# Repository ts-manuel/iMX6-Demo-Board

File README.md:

# i.MX6 Demo Board

<!-- TABLE OF CONTENTS -->
<details open="open">
  <summary>Table of Contents</summary>
  <ol>
    <li><a href="#about-the-project">About The Project</a></li>
    <li><a href="#hardware-specifications">Hardware Specifications</a></li>
    <li><a href="#software">Software</a></li>
    <li><a href="#schematic">Schematic</a></li>
  </ol>
</details>

<!-- ABOUT THE PROJECT -->
## About The Project
This repository contains the design files and documentation for a custom-built Linux demo board based on the NXP i.MX6ULL (900 MHz ARM Cortex-A7). The purpose of this project isn't to solve a specific problem or build a commercial product. This is a dedicated learning platform designed to bridge the gap between simple micro-controllers and complex application processors. While micro-controllers (like STM32 or ESP32) are great for real-time tasks, application processors are better suited for "heavy lifting" and high-level software stacks. Checkout the full schematic [schematic](./kicad/schematic/iMX6%20Demo%20Board.pdf) and the <a href="https://htmlpreview.github.io/?https://github.com/ts-manuel/iMX6-Demo-Board/blob/main/kicad/bom/ibom.html" target="_blank">Interactive BOM</a>.

### Hardware Specifications
- **System**
    - CPU: NXP i.MX6ULL @ 900 MHz (ARM Cortex-A7)
    - RAM: 512 MB DDR3
- **Storage:**
    - 4 GB eMMC (On-board)
    - 32 MB NOR Quad SPI
    - Micro SD-Card Slot
- **Connectivity:**
    - 1x 100Mb Ethernet
    - 2x USB 2.0 Host (Type A)
    - 1x USB 2.0 Device (Type C)
    - 2x Audio Jacks 3.5 mm (WM8904 Codec)
- **UI & Indicators:**
    - 24-bit LCD Interface
    - 8x User LEDs + 5x Status LEDs

<!-- SOFTWARE -->
## Software
The current goal is to compile a basic Linux image using the Yocto Project to exercise and validate every hardware feature on the board (Ethernet, USB, Display, and GPIO).

**Status: In Progress**. Development of the custom meta-layer and bitbake recipes is currently underway.

<!-- SCHEMATIC -->
## Schematic
Checkout the full [schematic](./kicad/schematic/iMX6%20Demo%20Board.pdf) in PDF.

### POWER TREE

### BLOCK DIAGRAM

### POWER

### CPU

### RAM DDR3

### eMMC QSPI SD

### USB TYPE A

### ETHERNET

### AUDIO CODEC

### LCD

### BOOT CONFIG

### CONTROL GPIO

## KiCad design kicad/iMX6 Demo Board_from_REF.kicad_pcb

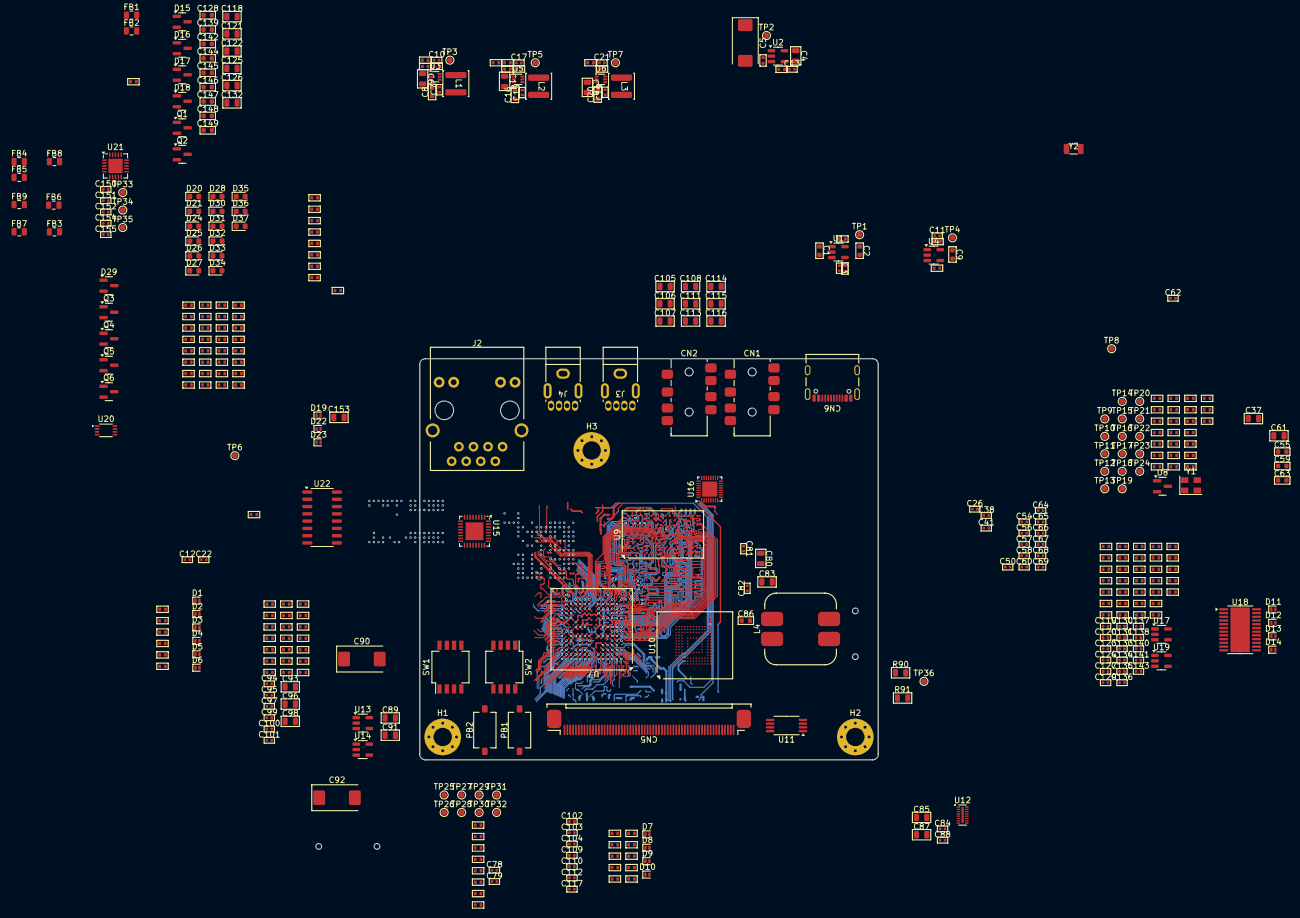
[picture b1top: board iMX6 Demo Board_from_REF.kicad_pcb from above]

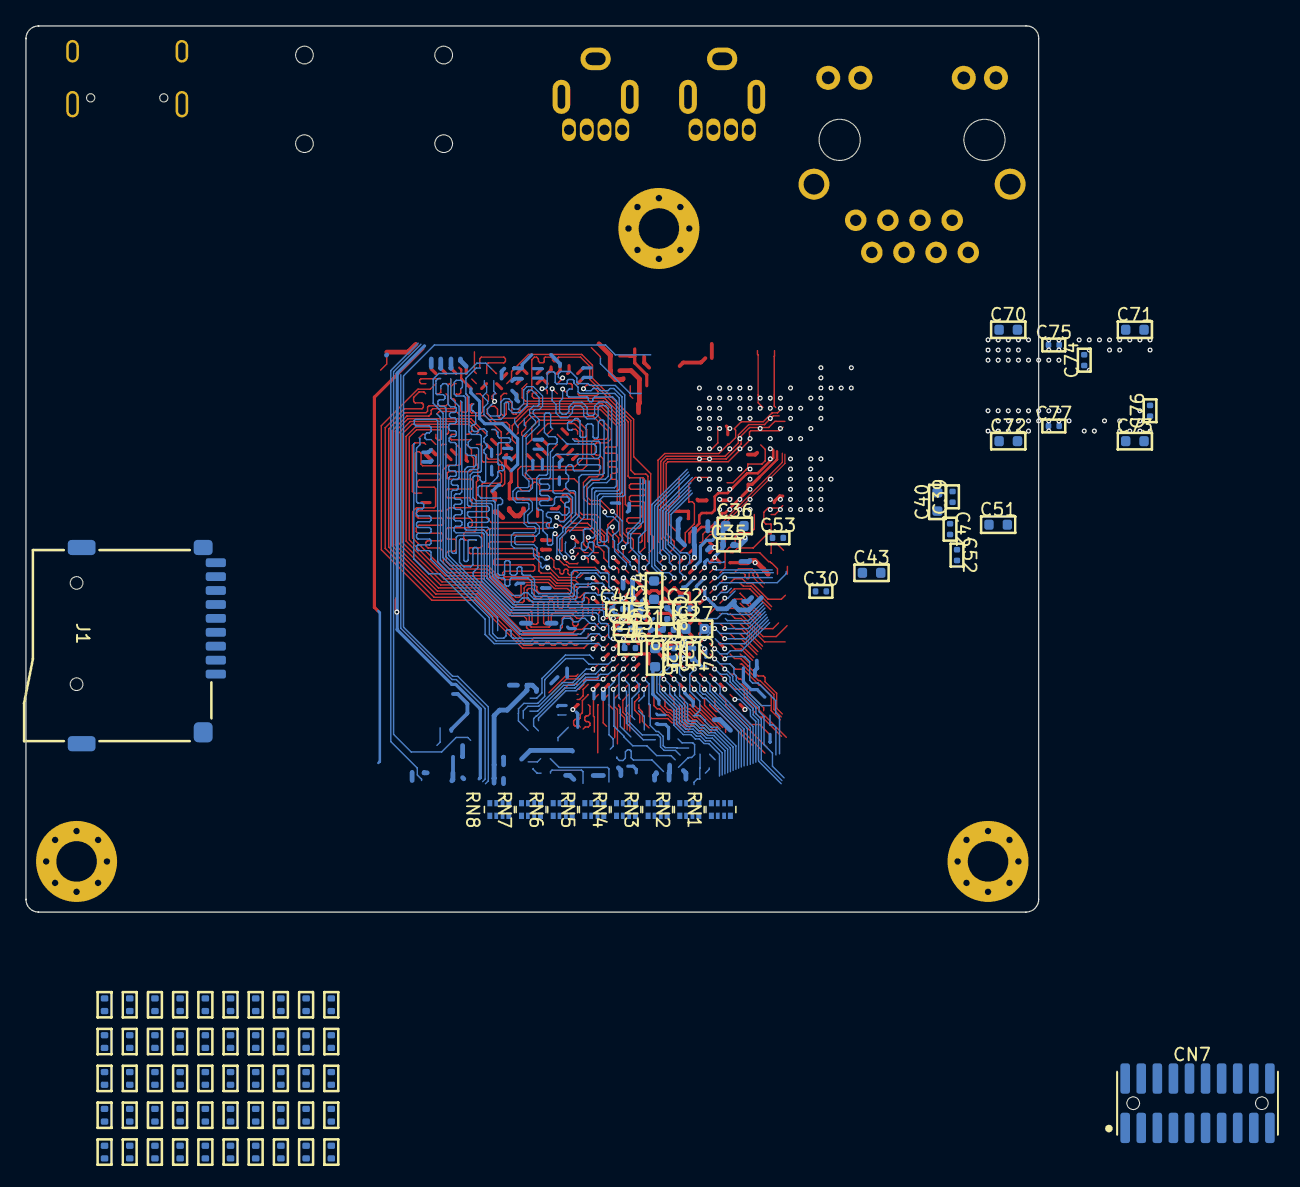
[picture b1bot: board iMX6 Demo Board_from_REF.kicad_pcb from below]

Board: 6 copper layers, 80.0 x 70.0 mm, 504 parts (91 on the bottom side), 405 nets.

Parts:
C1, C2, C8, C9, C16, C20, C55, C59, C63, C86, C128, C139, C142, C144, C145, C146, C147, C148, C149: 1 uF; CAP-0603
C3: 220 pF; CAP-0402
C4, C6, C14, C18, C80, C83, C85, C87, C89, C91, C98, C105, C106, C107, C108, C111, C113, C114, C115, C116, C118, C121, C122, C125, C126, C132, C153: 2.2 uF; CAP-0805
C5, C90, C92: 150 uF; CP_EIA-7343-31_Kemet-D
C7, C12, C13, C15, C19, C26, C50, C56, C57, C58, C60, C62, C64, C69, C78, C79, C81, C82, C84, C88, C94, C95, C97, C99, C100, C101, C102, C103, C104, C109, C110, C112, C117, C119, C120, C127, C130, C131, C133, C135, C140, C141, C143, C150, C151, C152, C154, C155: 100 nF; CAP-0402
C10, C17, C21, C65, C66, C67, C68, C123, C124, C129, C136: 22 pF; CAP-0402
C11: 560 pF; CAP-0402
C22, C134, C137, C138: 2.2 nF; CAP-0402
C23, C24, C28, C29, C30, C31, C32, C33, C35, C38, C39, C41, C42, C44, C45, C46, C52, C53, C54, C74, C75, C76, C77: 220 nF; CAP-0402
C25, C27, C34: 22 uF; CAP-0603
C36, C40, C43: 10 uF; CAP-0603
C37, C61, C93, C96: 22 uF; CAP-0805
C51, C70, C71, C72, C73: 2.2 uF; CAP-0603
CN1, CN2: PJ-393 8PJ; Jack_SMD_3.5mm_PJ-393-8PJ
CN5: KH-CL0.5-H2.0-60PS; CN-FPC-KH-CL0.5-H2.0-60PS
CN6: USB4105-GF-A; USB-TYPE-C-12P
CN7: 20021121-00020C4LF; CN-SMD-2x10P-1.27MM-FR
D1, D2, D3, D4, D5, D6, D7, D8, D9, D10, D11, D12, D13, D14, D19, D22, D23: LESD8D5.0CAT5G; D_SOD-882
D15, D16, D17, D18, D29: BAT54S; SOT-23
D20, D24: 150060RS75003; LED_0603_1608Metric
D21, D25, D26, D27, D28, D30, D31, D32, D33, D34, D35, D36, D37: 150060VS75000; LED_0603_1608Metric
FB1, FB2, FB3, FB4, FB5, FB6, FB7, FB8, FB9: GZ2012D101TF; FB-0805
H1, H2, H3: MountingHole_Pad; MountingHole_3.2mm_M3_Pad_Via
J1: GT-TF003-H0185-01; MicroSD_G-Switch _GT-TF003-H0185-01
J2: HR911105A; RJ45_THT-HR911105A
J3, J4: 906-762B1026D10200; USB-TypeA-906-762B1026D10200
L1, L2, L3: 27 uH; IND-SMD-FNR4020S
L4: 6.8 uH; IND-SMD-ACPR1208S
PB1, PB2: PTS636 SK25 SMTR LFS; BTN_SMD_PTS636-SK25-SMTR-LFS
Q1: NTR5105PT1G; SOT-23
Q2, Q3, Q4, Q5, Q6: SMMBT3904LT1G; SOT-23
R1: 56.2K; RES-0402
R2, R6, R8, R9, R10: 18K; RES-0402
R3, R5, R11, R12, R15, R116: 82K; RES-0402
R4: 24K; RES-0402
R7, R18, R19, R20, R23, R24, R29, R43, R44, R45, R49, R50, R51, R52, R53, R54, R55, R56, R57, R58, R61, R66, R67, R68, R72, R73, R74, R78, R79, R84, R86, R89, R92, R93, R94, R97, R98, R131, R132, R133, R134, R135, R136, R137, R138, R139, R140, R141, R142, R143, R144, R145, R146, R147, R148, R149, R150, R155, R156, R157, R158, R159, R160, R161, R162, R163, R164, R165, R166, R167, R168, R169, R170, R171, R172, R173, R174, R175, R176, R177, R178, R179, R180, R197, R198, R199, R200, R201, R202, R211, R212: 10K; RES-0402
R13: 72K; RES-0402
R14: 820R; RES-0402
R16: 64.9K; RES-0402
R17, R41, R42: 240R; RES-0402
R21, R25, R26, R104, R105, R107, R108, R109, R117, R119, R120, R123, R126: 0R; RES-0402
R22, R46, R47, R59, R60, R62, R69, R70, R71, R75, R76, R77, R80, R81, R82, R83, R85, R111, R112, R151, R152, R153, R154, R187, R188: 1.5K; RES-0402
R27, R28, R30, R31, R32, R33, R34, R35, R36, R37, R40: 1M; RES-0402
R38, R87, R88, R95, R96, R181, R182, R183, R184, R185, R186: 22R; RES-0402
R39, R63, R64, R99, R100, R101, R106, R191, R192, R193, R194, R195, R196, R203, R204, R205, R206, R207, R208, R209, R210: 220R; RES-0402
R48: 470R; RES-0402
R65: 6.49K; RES-0402
R90, R91: 100K; RES-0805
R102, R115: 62K; RES-0402
R103, R113, R114, R118: 680K; RES-0402
R110, R121, R122, R124, R125, R127, R128, R129, R130: 47K; RES-0402
R189, R190: 5.1K; RES-0402
RN1, RN2, RN3, RN4, RN5, RN6, RN7, RN8: 4x22R; R_Array_Convex_4x0402
SW1, SW2: EP-04KS; SW_DIP_SPSTx04_Slide_Copal_CHS-04B_W7.62mm_P1.27mm
TP1, TP2, TP3, TP4, TP5, TP6, TP7, TP8, TP9, TP10, TP11, TP12, TP13, TP14, TP15, TP16, TP17, TP18, TP19, TP20, TP21, TP22, TP23, TP24, TP25, TP26, TP27, TP28, TP29, TP30, TP31, TP32, TP33, TP34, TP35, TP36: TestPoint_Pad_D1.0mm
U1, U4: AP2127K-ADJTRG1; SOT-23-5
U2, U13, U14, U17: MT9700; SOT-23-5
U3, U5, U6: SY8892ARC; SOT-563
U7: MCIMX6Y2CVM08AB; BGA-289P08L17x17_14.0x14.0mm_Ball0.35mm_Pad0.30mm
U8: UM803RS; SOT-23
U9: MT41K256M16TW-107; BGA-96P08L9X16_8.0X14.0mm_Ball0.45_Pad0.40mm
U10: THGBMNG5D1LBAIL; BGA-153_13.0x11.5mm_Ball0.30mm_Pad0.25mm
U11: ZD25WQ80BOIGT; TSSOP-8_4.4x3mm_P0.65mm
U12: IP4252CZ16-8-TTL; Nexperia_HUSON-16_USON-16-1EP_1.35x3.3mm_P0.4mm_EP0.4x2.8mm
U15: KSZ8081RNBIA-TR; QFN-32-1EP_5x5mm_P0.5mm_EP3.1x3.1mm
U16: WM8904CGEFL/RV; QFN-32-1EP_4x4mm_P0.4mm_EP2.65x2.65mm
U18: TPS65150PWPR; HTSSOP-24-1EP_4.4x7.8mm_P0.65mm_EP3.4x7.8mm_Mask2.4x4.68mm
U19: LMV321IDBVR; SOT-23-5
U20: TXS0102DCUR; VSSOP-8_2.3x2mm_P0.5mm
U21: FT231XQ; QFN-20-1EP_4x4mm_P0.5mm_EP2.5x2.5mm
U22: 74HC595D,118; SO-16_3.9x9.9mm_P1.27mm
Y1: 24 MHz; Crystal_SMD_EuroQuartz_MT-4Pin_3.2x2.5mm
Y2: 32.768 KHz; QUARTZ-SC-32S32.768kHz20PPM12.5pF

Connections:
+1.8V: C9.1, C11.2, C26.1, C56.1, C80.1, C81.1, C84.1, C85.1, C102.2, C103.2, C107.1, C108.1, C109.2, FB7.1, R4.2, R49.1, R92.1, R93.1, TP4.1, U4.5 (VOUT), U7.E7 (NVCC_NAND), U7.F4 (NVCC_CSI), U10.C6 (VCCQ), U10.M4 (VCCQ), U10.N4 (VCCQ), U10.P3 (VCCQ), U10.P5 (VCCQ), U11.8 (VCC), U16.4 (DBVDD), U16.6 (DCVDD), U16.7 (CPVDD), U16.19 (MICVDD)
+3V3_DCDC: C7.1, C8.1, C10.2, C50.1, C62.1, C63.1, C64.1, C69.1, C82.1, C83.1, C93.1, C94.2, C152.1, CN7.2, FB1.1, FB2.1, FB3.1, FB6.2, J2.9 (GA), J2.12 (YA), L1.2, R5.2, R23.1, R24.1, R50.2, R51.2, R52.2, R53.2, R54.2, R55.2, R56.2, R59.1, R60.1, R61.1, R62.1, R66.2, R67.2, R68.2, R72.2, R73.2, R74.2, R78.2, R79.2, R84.2, R119.1, R131.1, R132.1, R133.1, R134.1, R135.1, R136.1, R137.1, R138.1, R139.1, R140.1, R141.1, R142.1, R143.1, R144.1, R145.1, R146.1, R147.1, R148.1, R149.1, R150.1, R151.1, R152.1, R153.1, R154.1, R155.1, R156.1, R191.1, R192.1, R193.1, R194.1, R195.1, R196.1, R203.1, R204.1, R205.1, R206.1, R207.1, R208.1, R209.1, R210.1, R211.1, TP3.1, U4.1 (VDD), U7.C4 (NVCC_SD1), U7.E13 (NVCC_LCD), U7.F13 (NVCC_ENET), U7.H13 (NVCC_UART), U7.J13 (NVCC_GPIO), U8.3 (VCC), U10.E6 (VCC), U10.F5 (VCC), U10.J10 (VCC), U10.K9 (VCC), U15.17 (VDDIO), U20.3 (VCCA), U22.16 (VCC)
+3V3_FTDI: C150.1, C151.1, C155.2, R187.2, R188.2, U20.7 (VCCB), U21.10 (3V3OUT), U21.11 (~REST), U21.20 (VCCIO)
+3V3_STAND_BY: C2.1, C3.2, C41.1, R1.2, TP1.1, U1.5 (VOUT), U7.P12 (VDD_SNVS_IN)
+5V_LCD: C119.1, C140.1, FB8.1, R124.2, R125.2, U17.1 (VOUT)
+5V_VBUS: C1.1, C4.1, C89.1, C91.1, C118.1, CN6.2 (VBUS), CN6.11 (VBUS), D19.2 (A2), FB9.1, U1.1 (VDD), U1.3 (EN), U2.5 (VIN), U13.5 (VIN), U14.5 (VIN), U17.5 (VIN)
+5V_VBUS_USB1: C55.1, C90.1, FB4.1, U7.T12 (USB_OTG1_VBUS), U13.1 (VOUT)
+5V_VBUS_USB2: C59.1, C92.1, FB5.1, U7.U12 (USB_OTG2_VBUS), U14.1 (VOUT)
+VDD_DRAM: C19.1, C20.1, C21.2, C43.1, C44.1, C45.1, C46.1, C70.1, C71.1, C72.1, C73.1, C74.1, C75.1, C76.1, C77.1, C78.1, L3.2, R15.2, R46.1, TP7.1, U7.G6 (NVCC_DRAM), U7.H6 (NVCC_DRAM), U7.J6 (NVCC_DRAM), U7.K6 (NVCC_DRAM), U7.L6 (NVCC_DRAM), U7.M6 (NVCC_DRAM), U9.A1 (VDDQ), U9.A8 (VDDQ), U9.B2 (VDD), U9.C1 (VDDQ), U9.C9 (VDDQ), U9.D2 (VDDQ), U9.D9 (VDD), U9.E9 (VDDQ), U9.F1 (VDDQ), U9.G7 (VDD), U9.H2 (VDDQ), U9.H9 (VDDQ), U9.K2 (VDD), U9.K8 (VDD), U9.N1 (VDD), U9.N9 (VDD), U9.R1 (VDD), U9.R9 (VDD)
+VDD_HIGH_CAP: C35.1, C36.1, C53.1, TP10.1, U7.N6 (NVCC_DRAM_2P5), U7.R14 (VDD_HIGH_CAP), U7.R15 (VDD_HIGH_CAP)
+VDD_SOC: C15.1, C16.1, C17.2, C27.1, C28.1, C29.1, C30.1, L2.2, R12.2, TP5.1, U7.H9 (VDD_SOC_IN), U7.H10 (VDD_SOC_IN), U7.J9 (VDD_SOC_IN), U7.J10 (VDD_SOC_IN), U7.K9 (VDD_SOC_IN), U7.K10 (VDD_SOC_IN)
/i.MX6ULL MAIN/AUDIO CODEC/I2C1.SCL: R92.2, U7.E5 (CSI_PIXCLK), U16.2 (SCLK)
/i.MX6ULL MAIN/AUDIO CODEC/I2C1.SDA: R93.2, U7.F5 (CSI_MCLK), U16.3 (SDA)
/i.MX6ULL MAIN/AUDIO CODEC/I2S_ADCDAT: U7.D2 (CSI_DATA06), U16.31 (ADCDAT)
/i.MX6ULL MAIN/AUDIO CODEC/I2S_BCLK: U7.D3 (CSI_DATA05), U16.29 (BCLK_/_GPIO4)
/i.MX6ULL MAIN/AUDIO CODEC/I2S_DACDAT: U7.D1 (CSI_DATA07), U16.32 (DACDAT)
/i.MX6ULL MAIN/AUDIO CODEC/I2S_LRCLK: U7.D4 (CSI_DATA04), U16.30 (LRCLK)
/i.MX6ULL MAIN/AUDIO CODEC/I2S_MCLK: U7.E3 (CSI_DATA01), U16.28 (MCLK)
/i.MX6ULL MAIN/BOOT CONFIG/BOOT_MODE_0: SW2.2, U7.T10 (BOOT_MODE0)
/i.MX6ULL MAIN/BOOT CONFIG/BOOT_MODE_1: SW2.1, U7.U10 (BOOT_MODE1)
/i.MX6ULL MAIN/BOOT CONFIG/LCD_DATA0: R157.1, RN2.6 (R3.2), SW1.4, U7.B9 (LCD_DATA00)
/i.MX6ULL MAIN/BOOT CONFIG/LCD_DATA1: R150.2, R158.1, RN2.7 (R2.2), U7.A9 (LCD_DATA01)
/i.MX6ULL MAIN/BOOT CONFIG/LCD_DATA2: R149.2, R159.1, RN2.8 (R1.2), U7.E10 (LCD_DATA02)
/i.MX6ULL MAIN/BOOT CONFIG/LCD_DATA3: R148.2, R160.1, RN3.5 (R4.2), U7.D10 (LCD_DATA03)
/i.MX6ULL MAIN/BOOT CONFIG/LCD_DATA4: R147.2, R161.1, RN3.6 (R3.2), U7.C10 (LCD_DATA04)
/i.MX6ULL MAIN/BOOT CONFIG/LCD_DATA5: R162.1, RN3.7 (R2.2), SW1.3, U7.B10 (LCD_DATA05)
/i.MX6ULL MAIN/BOOT CONFIG/LCD_DATA6: R163.1, RN3.8 (R1.2), SW1.2, U7.A10 (LCD_DATA06)
/i.MX6ULL MAIN/BOOT CONFIG/LCD_DATA7: R164.1, RN4.5 (R4.2), SW1.1, U7.D11 (LCD_DATA07)
/i.MX6ULL MAIN/BOOT CONFIG/LCD_DATA8: R146.2, R165.1, RN4.6 (R3.2), U7.B11 (LCD_DATA08)
/i.MX6ULL MAIN/BOOT CONFIG/LCD_DATA9: R145.2, R166.1, RN4.7 (R2.2), U7.A11 (LCD_DATA09)
/i.MX6ULL MAIN/BOOT CONFIG/LCD_DATA10: R144.2, R167.1, RN4.8 (R1.2), U7.E12 (LCD_DATA10)
/i.MX6ULL MAIN/BOOT CONFIG/LCD_DATA11: R143.2, R168.1, RN5.5 (R4.2), U7.D12 (LCD_DATA11)
/i.MX6ULL MAIN/BOOT CONFIG/LCD_DATA12: R142.2, R169.1, RN5.6 (R3.2), U7.C12 (LCD_DATA12)
/i.MX6ULL MAIN/BOOT CONFIG/LCD_DATA13: R141.2, R170.1, RN5.7 (R2.2), U7.B12 (LCD_DATA13)
/i.MX6ULL MAIN/BOOT CONFIG/LCD_DATA14: R140.2, R171.1, RN5.8 (R1.2), U7.A12 (LCD_DATA14)
/i.MX6ULL MAIN/BOOT CONFIG/LCD_DATA15: R139.2, R172.1, RN6.5 (R4.2), U7.D13 (LCD_DATA15)
/i.MX6ULL MAIN/BOOT CONFIG/LCD_DATA16: R138.2, R173.1, RN6.6 (R3.2), U7.C13 (LCD_DATA16)
/i.MX6ULL MAIN/BOOT CONFIG/LCD_DATA17: R137.2, R174.1, RN6.7 (R2.2), U7.B13 (LCD_DATA17)
/i.MX6ULL MAIN/BOOT CONFIG/LCD_DATA18: R136.2, R175.1, RN6.8 (R1.2), U7.A13 (LCD_DATA18)
/i.MX6ULL MAIN/BOOT CONFIG/LCD_DATA19: R135.2, R176.1, RN7.5 (R4.2), U7.D14 (LCD_DATA19)
/i.MX6ULL MAIN/BOOT CONFIG/LCD_DATA20: R134.2, R177.1, RN7.6 (R3.2), U7.C14 (LCD_DATA20)
/i.MX6ULL MAIN/BOOT CONFIG/LCD_DATA21: R133.2, R178.1, RN7.7 (R2.2), U7.B14 (LCD_DATA21)
/i.MX6ULL MAIN/BOOT CONFIG/LCD_DATA22: R132.2, R179.1, RN7.8 (R1.2), U7.A14 (LCD_DATA22)
/i.MX6ULL MAIN/BOOT CONFIG/LCD_DATA23: R131.2, R180.1, RN8.5 (R4.2), U7.B16 (LCD_DATA23)
/i.MX6ULL MAIN/BOOT CONFIG/LCD_DOTCLK: CN5.44, RN8.1 (R1.1), RN8.8 (R1.2), U7.A8 (LCD_CLK)
/i.MX6ULL MAIN/BOOT CONFIG/LCD_HSYNC: CN5.42, RN8.3 (R3.1), RN8.6 (R3.2), U7.D9 (LCD_HSYNC)
/i.MX6ULL MAIN/BOOT CONFIG/LCD_RESET: CN5.14, RN1.3 (R3.1), RN1.6 (R3.2), U7.E9 (LCD_RESET)
/i.MX6ULL MAIN/BOOT CONFIG/LCD_VSYNC: CN5.43, RN8.2 (R2.1), RN8.7 (R2.2), U7.C9 (LCD_VSYNC)
/i.MX6ULL MAIN/CONTROL GPIO/FTDI_RX: D21.1 (K), R183.1, TP34.1, U21.1 (RXD)
/i.MX6ULL MAIN/CONTROL GPIO/FTDI_TX: D20.1 (K), R181.1, TP33.1, U21.17 (TXD)
/i.MX6ULL MAIN/CONTROL GPIO/JTAG_DACK: CN7.19, R201.1
/i.MX6ULL MAIN/CONTROL GPIO/JTAG_RTCK: CN7.11, R202.1
/i.MX6ULL MAIN/CONTROL GPIO/JTAG_TCK: CN7.9, U7.M14 (JTAG_TCK)
/i.MX6ULL MAIN/CONTROL GPIO/JTAG_TDI: CN7.5, U7.N16 (JTAG_TDI)
/i.MX6ULL MAIN/CONTROL GPIO/JTAG_TDO: CN7.13, U7.N15 (JTAG_TDO)
/i.MX6ULL MAIN/CONTROL GPIO/JTAG_TMS: CN7.7, U7.P14 (JTAG_TMS)
/i.MX6ULL MAIN/CONTROL GPIO/JTAG_VREF: CN7.1, R196.2
/i.MX6ULL MAIN/CONTROL GPIO/LED_ACTIVITY: R197.2, U7.G14 (~UART3_RTS)
/i.MX6ULL MAIN/CONTROL GPIO/LED_EMMC: R198.2, U7.H16 (UART3_RX_DATA)
/i.MX6ULL MAIN/CONTROL GPIO/LED_NETWORK: R200.2, U7.J15 (~UART2_CTS)
/i.MX6ULL MAIN/CONTROL GPIO/LED_SD: R199.2, U7.H17 (UART3_TX_DATA)
/i.MX6ULL MAIN/CONTROL GPIO/LED_SR_RCLK: U7.G17 (UART4_TX_DATA), U22.12 (RCLK)
/i.MX6ULL MAIN/CONTROL GPIO/LED_SR_SER: U7.G13 (UART5_RX_DATA), U22.14 (SER)
/i.MX6ULL MAIN/CONTROL GPIO/LED_SR_SRCLK: U7.F17 (UART5_TX_DATA), U22.11 (SRCLK)
/i.MX6ULL MAIN/CONTROL GPIO/PMIC_POWER_GOOD: R11.2, R21.2, TP6.1, U5.6 (PG), U6.6 (PG), U13.4 (EN), U14.4 (EN), U17.4 (EN), U20.6 (OE)
/i.MX6ULL MAIN/CONTROL GPIO/UART1.RX: R182.2, U7.K16 (UART1_RX_DATA)
/i.MX6ULL MAIN/CONTROL GPIO/UART1.TX: R184.2, U7.K14 (UART1_TX_DATA)
/i.MX6ULL MAIN/CONTROL GPIO/USBD_n: CN6.5 (DN2), CN6.7 (DN1), D22.2 (A2), R186.1
/i.MX6ULL MAIN/CONTROL GPIO/USBD_p: CN6.6 (DP1), CN6.8 (DP2), D23.2 (A2), R185.1
/i.MX6ULL MAIN/CONTROL GPIO/~JTAG_SRST: CN7.15, D29.3 (common)
/i.MX6ULL MAIN/CONTROL GPIO/~JTAG_TRST: CN7.3, U7.N14 (JTAG_TRST_B)
/i.MX6ULL MAIN/CONTROL GPIO/~LED_SR_SRCLR: U7.G16 (UART4_RX_DATA), U22.10 (~SRCLR)
/i.MX6ULL MAIN/CPU/DRAM_A0: TP28.1, U7.L5 (DRAM_ADDR00), U9.N3 (A0)
/i.MX6ULL MAIN/CPU/DRAM_A1: U7.H2 (DRAM_ADDR01), U9.P7 (A1)
/i.MX6ULL MAIN/CPU/DRAM_A2: U7.K1 (DRAM_ADDR02), U9.P3 (A2)
/i.MX6ULL MAIN/CPU/DRAM_A3: U7.M2 (DRAM_ADDR03), U9.N2 (A3)
/i.MX6ULL MAIN/CPU/DRAM_A4: U7.K4 (DRAM_ADDR04), U9.P8 (A4)
/i.MX6ULL MAIN/CPU/DRAM_A5: U7.L1 (DRAM_ADDR05), U9.P2 (A5)
/i.MX6ULL MAIN/CPU/DRAM_A6: U7.G2 (DRAM_ADDR06), U9.R8 (A6)
/i.MX6ULL MAIN/CPU/DRAM_A7: U7.H4 (DRAM_ADDR07), U9.R2 (A7)
/i.MX6ULL MAIN/CPU/DRAM_A8: U7.J4 (DRAM_ADDR08), U9.T8 (A8)
/i.MX6ULL MAIN/CPU/DRAM_A9: U7.L2 (DRAM_ADDR09), U9.R3 (A9)
/i.MX6ULL MAIN/CPU/DRAM_A10: U7.M4 (DRAM_ADDR10), U9.L7 (A10/AP)
/i.MX6ULL MAIN/CPU/DRAM_A11: U7.K3 (DRAM_ADDR11), U9.R7 (A11)
/i.MX6ULL MAIN/CPU/DRAM_A12: U7.L4 (DRAM_ADDR12), U9.N7 (A12/~BC)
/i.MX6ULL MAIN/CPU/DRAM_A13: U7.H3 (DRAM_ADDR13), U9.T3 (A13)
/i.MX6ULL MAIN/CPU/DRAM_A14: U7.G1 (DRAM_ADDR14), U9.T7 (A14)
/i.MX6ULL MAIN/CPU/DRAM_A15: U7.K5 (DRAM_ADDR15), U9.M7 (NC_(A15))
/i.MX6ULL MAIN/CPU/DRAM_BA0: U7.M1 (DRAM_SDBA0), U9.M2 (BA0)
/i.MX6ULL MAIN/CPU/DRAM_BA1: U7.H1 (DRAM_SDBA1), U9.N8 (BA1)
/i.MX6ULL MAIN/CPU/DRAM_BA2: U7.K2 (DRAM_SDBA2), U9.M3 (BA2)
/i.MX6ULL MAIN/CPU/DRAM_CLK_EN0: R19.1, R45.1, U7.M3 (DRAM_SDCKE0), U9.K9 (CKE0)
/i.MX6ULL MAIN/CPU/DRAM_CLK_EN1: R20.1, R44.1, U7.J3 (DRAM_SDCKE1), U9.J9 (NC_(CKE1))
/i.MX6ULL MAIN/CPU/DRAM_CLK_N: R48.2, TP32.1, U7.P2 (DRAM_SDCLK0_N), U9.K7 (~CK)
/i.MX6ULL MAIN/CPU/DRAM_CLK_P: R48.1, TP26.1, U7.P1 (DRAM_SDCLK0_P), U9.J7 (CK)
/i.MX6ULL MAIN/CPU/DRAM_ODT0: U7.N1 (DRAM_ODT0), U9.K1 (ODT0)
/i.MX6ULL MAIN/CPU/DRAM_ODT1: U7.F1 (DRAM_ODT1), U9.J1 (NC_(ODT1))
/i.MX6ULL MAIN/CPU/ENET_CLK: R38.2, U15.9 (XI)
/i.MX6ULL MAIN/CPU/LCD_BACK_LIGHT: R112.1, U7.H15 (~UART3_CTS)
/i.MX6ULL MAIN/CPU/LCD_SPI_MOSI: RN2.5 (R4.2), U7.B15 (ENET2_TX_EN)
/i.MX6ULL MAIN/CPU/LCD_SPI_SCLK: RN1.8 (R1.2), U7.A16 (ENET2_TX_DATA1)
/i.MX6ULL MAIN/CPU/NVCC_PLL: C39.1, C40.1, TP11.1, U7.P13 (NVCC_PLL)
/i.MX6ULL MAIN/CPU/ONOFF: C57.1, PB1.2, R23.2, U7.R8 (ONOFF)
/i.MX6ULL MAIN/CPU/PMIC_ON_REQ: R10.1, U7.T9 (SNVS_PMIC_ON_REQ)
/i.MX6ULL MAIN/CPU/QSPI_DATA0: U7.A3 (~NAND_READY), U11.5 (SI/DQ0)
/i.MX6ULL MAIN/CPU/QSPI_DATA1: U7.C5 (~NAND_CE0), U11.2 (SO/DQ1)
/i.MX6ULL MAIN/CPU/QSPI_DATA2: U7.B5 (~NAND_CE1), U11.3 (~WP/DQ2)
/i.MX6ULL MAIN/CPU/QSPI_DATA3: U7.A4 (NAND_CLE), U11.7 (~HOLD/DQ3)
/i.MX6ULL MAIN/CPU/QSPI_SCLK: U7.D5 (~NAND_WP), U11.6 (SCLK)
/i.MX6ULL MAIN/CPU/RMII_CRS_DV/CONFIG2: R74.1, R77.1, U7.E16 (ENET1_RX_EN), U15.18 (CRS_DV/CONFIG2)
/i.MX6ULL MAIN/CPU/RMII_MDC: R59.2, U7.C16 (ENET2_RX_DATA1), U15.12 (MDC)
/i.MX6ULL MAIN/CPU/RMII_MDIO: R60.2, U7.C17 (ENET2_RX_DATA0), U15.11 (MDIO)
/i.MX6ULL MAIN/CPU/RMII_RXD0/DUPLEX: R83.1, U7.F16 (ENET1_RX_DATA0), U15.16 (RXD0/DUPLEX)
/i.MX6ULL MAIN/CPU/RMII_RXD1/PHYAD2: R68.1, R71.1, U7.E17 (ENET1_RX_DATA1), U15.15 (RXD1/PHYAD2)
/i.MX6ULL MAIN/CPU/RMII_RXER/ISO: R78.1, R80.1, U7.D15 (ENET1_RX_ER), U15.20 (RXER/ISO)
/i.MX6ULL MAIN/CPU/RMII_TXD0: U7.E15 (ENET1_TX_DATA0), U15.24 (TXD0)
/i.MX6ULL MAIN/CPU/RMII_TXD1: U7.E14 (ENET1_TX_DATA1), U15.25 (TXD1)
/i.MX6ULL MAIN/CPU/RMII_TXEN: U7.F15 (ENET1_TX_EN), U15.23 (TXEN)
/i.MX6ULL MAIN/CPU/SD_CARD_CMD: R54.1, U7.C2 (SD1_CMD), U12.3 (CH3)
/i.MX6ULL MAIN/CPU/SD_CARD_DATA0: R52.1, U7.B3 (SD1_DATA0), U12.5 (CH5)
/i.MX6ULL MAIN/CPU/SD_CARD_DATA1: R51.1, U7.B2 (SD1_DATA1), U12.6 (CH6)
/i.MX6ULL MAIN/CPU/SD_CARD_DATA2: R56.1, U7.B1 (SD1_DATA2), U12.1 (CH1)
/i.MX6ULL MAIN/CPU/SD_CARD_DATA3: R55.1, U7.A2 (SD1_DATA3), U12.2 (CH2)
/i.MX6ULL MAIN/CPU/SD_CARD_SCLK: R53.1, U7.C1 (SD1_CLK), U12.4 (CH4)
/i.MX6ULL MAIN/CPU/TOUCH.X1: D14.2 (A2), R104.1, U7.L17 (GPIO1_IO03)
/i.MX6ULL MAIN/CPU/TOUCH.X2: D12.2 (A2), R107.1, U7.M16 (GPIO1_IO04)
/i.MX6ULL MAIN/CPU/TOUCH.Y1: D13.2 (A2), R105.1, U7.L15 (GPIO1_IO01)
/i.MX6ULL MAIN/CPU/TOUCH.Y2: D11.2 (A2), R108.1, U7.L14 (GPIO1_IO02)
/i.MX6ULL MAIN/CPU/USB1.DN: D3.2 (A2), J3.3 (D+), U7.T15 (USB_OTG1_DN)
/i.MX6ULL MAIN/CPU/USB1.DP: D2.2 (A2), J3.2 (D-), U7.U15 (USB_OTG1_DP)
/i.MX6ULL MAIN/CPU/USB2.DN: D6.2 (A2), J4.3 (D+), U7.T13 (USB_OTG2_DN)
/i.MX6ULL MAIN/CPU/USB2.DP: D5.2 (A2), J4.2 (D-), U7.U13 (USB_OTG2_DP)
/i.MX6ULL MAIN/CPU/VDD_ARM_CAP: C23.1, C24.1, C25.1, TP8.1, U7.G9 (VDD_ARM_CAP), U7.G10 (VDD_ARM_CAP), U7.G11 (VDD_ARM_CAP), U7.H11 (VDD_ARM_CAP)
/i.MX6ULL MAIN/CPU/VDD_SNVS_CAP: C42.1, TP12.1, U7.N12 (VDD_SNVS_CAP)
/i.MX6ULL MAIN/CPU/VDD_SOC_CAP: C31.1, C32.1, C33.1, C34.1, TP9.1, U7.G8 (VDD_SOC_CAP), U7.H8 (VDD_SOC_CAP), U7.J8 (VDD_SOC_CAP), U7.J11 (VDD_SOC_CAP), U7.K8 (VDD_SOC_CAP), U7.K11 (VDD_SOC_CAP), U7.L8 (VDD_SOC_CAP), U7.L9 (VDD_SOC_CAP), U7.L10 (VDD_SOC_CAP), U7.L11 (VDD_SOC_CAP)
/i.MX6ULL MAIN/CPU/eMMC_CLK: U7.D8 (~NAND_RE), U10.M6 (CLK)
/i.MX6ULL MAIN/CPU/eMMC_CMD: U7.C8 (~NAND_WE), U10.M5 (CMD)
/i.MX6ULL MAIN/CPU/eMMC_DATA0: U7.D7 (NAND_DATA00), U10.A3 (DAT0)
/i.MX6ULL MAIN/CPU/eMMC_DATA1: U7.B7 (NAND_DATA01), U10.A4 (DAT1)
/i.MX6ULL MAIN/CPU/eMMC_DATA2: U7.A7 (NAND_DATA02), U10.A5 (DAT2)
/i.MX6ULL MAIN/CPU/eMMC_DATA3: U7.D6 (NAND_DATA03), U10.B2 (DAT3)
/i.MX6ULL MAIN/CPU/eMMC_DATA4: U7.C6 (NAND_DATA04), U10.B3 (DAT4)
/i.MX6ULL MAIN/CPU/eMMC_DATA5: U7.B6 (NAND_DATA05), U10.B4 (DAT5)
/i.MX6ULL MAIN/CPU/eMMC_DATA6: U7.A6 (NAND_DATA06), U10.B5 (DAT6)
/i.MX6ULL MAIN/CPU/eMMC_DATA7: U7.A5 (NAND_DATA07), U10.B6 (DAT7)
/i.MX6ULL MAIN/CPU/~DRAM_CAS: U7.J2 (~DRAM_CAS), U9.K3 (~CAS)
/i.MX6ULL MAIN/CPU/~DRAM_CS0: U7.N2 (~DRAM_CS0), U9.L2 (~CS0)
/i.MX6ULL MAIN/CPU/~DRAM_CS1: U7.H5 (~DRAM_CS1), U9.L1 (NC_(~CS1))
/i.MX6ULL MAIN/CPU/~DRAM_RAS: U7.M5 (~DRAM_RAS), U9.J3 (~RAS)
/i.MX6ULL MAIN/CPU/~DRAM_WE: U7.J1 (~DRAM_SDWE), U9.L3 (~WE)
/i.MX6ULL MAIN/CPU/~LCD_SPI_CS: RN1.7 (R2.2), U7.D16 (ENET2_RX_ER)
/i.MX6ULL MAIN/CPU/~POWER_ON_RESET: C58.1, D29.1 (A), PB2.2, R21.1, R22.2, R24.2, U7.P8 (~POR)
/i.MX6ULL MAIN/CPU/~QSPI_CS: R49.2, U7.E6 (NAND_DQS), U11.1 (~CS)
/i.MX6ULL MAIN/CPU/~SD_CARD_CD: R50.1, U7.J14 (~UART1_RTS), U12.8 (CH8)
/i.MX6ULL MAIN/CPU/~eMMC_RESET: U7.B4 (NAND_ALE), U10.K5 (~REST)
/i.MX6ULL MAIN/ETHERNET/+1V2_ENET: C97.2, C98.1, U15.2 (VDD_1.2)
/i.MX6ULL MAIN/ETHERNET/B-CAST_OFF: R84.1, U15.19 (REF_CLK/B-CAST_OFF)
/i.MX6ULL MAIN/ETHERNET/CONFIG0: R72.1, R75.1, U15.28 (CONFIG0)
/i.MX6ULL MAIN/ETHERNET/CONFIG1: R73.1, R76.1, U15.29 (CONFIG1)
/i.MX6ULL MAIN/ETHERNET/ENET_INTRP/~NAND_TREE: R26.1, R62.2, R85.1, U15.21 (INTRP/~NAND_TREE)
/i.MX6ULL MAIN/ETHERNET/NWAYEN: R63.1, R81.1, U15.30 (LED0/NWAYEN)
/i.MX6ULL MAIN/ETHERNET/PHYAD0: R66.1, R69.1, U15.13 (PHYAD0)
/i.MX6ULL MAIN/ETHERNET/PHYAD1: R67.1, R70.1, U15.14 (PHYAD1)
/i.MX6ULL MAIN/ETHERNET/SPEED: R64.1, R79.1, R82.1, U15.31 (LED1/SPEED)
/i.MX6ULL MAIN/ETHERNET/~ENET_RST: C101.2, R61.2, U7.L16 (GPIO1_IO07), U15.32 (~RST)
/i.MX6ULL MAIN/LCD/CAP1: C144.1, CN5.55
/i.MX6ULL MAIN/LCD/CAP2: C145.1, CN5.54
/i.MX6ULL MAIN/LCD/CAP3: C146.1, CN5.52
/i.MX6ULL MAIN/LCD/CAP4: C147.1, CN5.49
/i.MX6ULL MAIN/LCD/CAP5: C148.1, CN5.12
/i.MX6ULL MAIN/LCD/CAP6: C149.1, CN5.11
/i.MX6ULL MAIN/LCD/LCD_B0: CN5.18, RN2.3 (R3.1)
/i.MX6ULL MAIN/LCD/LCD_B1: CN5.19, RN2.2 (R2.1)
/i.MX6ULL MAIN/LCD/LCD_B2: CN5.20, RN2.1 (R1.1)
/i.MX6ULL MAIN/LCD/LCD_B3: CN5.21, RN3.4 (R4.1)
/i.MX6ULL MAIN/LCD/LCD_B4: CN5.22, RN3.3 (R3.1)
/i.MX6ULL MAIN/LCD/LCD_B5: CN5.23, RN3.2 (R2.1)
/i.MX6ULL MAIN/LCD/LCD_B6: CN5.24, RN3.1 (R1.1)
/i.MX6ULL MAIN/LCD/LCD_B7: CN5.25, RN4.4 (R4.1)
/i.MX6ULL MAIN/LCD/LCD_CS_n: CN5.15, RN1.2 (R2.1)
/i.MX6ULL MAIN/LCD/LCD_G0: CN5.26, RN4.3 (R3.1)
/i.MX6ULL MAIN/LCD/LCD_G1: CN5.27, RN4.2 (R2.1)
/i.MX6ULL MAIN/LCD/LCD_G2: CN5.28, RN4.1 (R1.1)
/i.MX6ULL MAIN/LCD/LCD_G3: CN5.29, RN5.4 (R4.1)
/i.MX6ULL MAIN/LCD/LCD_G4: CN5.30, RN5.3 (R3.1)
/i.MX6ULL MAIN/LCD/LCD_G5: CN5.31, RN5.2 (R2.1)
/i.MX6ULL MAIN/LCD/LCD_G6: CN5.32, RN5.1 (R1.1)
/i.MX6ULL MAIN/LCD/LCD_G7: CN5.33, RN6.4 (R4.1)
/i.MX6ULL MAIN/LCD/LCD_LED_A: C122.1, CN5.1, CN5.2, R99.2, R100.2, R101.2
/i.MX6ULL MAIN/LCD/LCD_M: CN5.13, RN1.4 (R4.1)
/i.MX6ULL MAIN/LCD/LCD_MOSI: CN5.17, RN2.4 (R4.1)
/i.MX6ULL MAIN/LCD/LCD_R0: CN5.34, RN6.3 (R3.1)
/i.MX6ULL MAIN/LCD/LCD_R1: CN5.35, RN6.2 (R2.1)
/i.MX6ULL MAIN/LCD/LCD_R2: CN5.36, RN6.1 (R1.1)
/i.MX6ULL MAIN/LCD/LCD_R3: CN5.37, RN7.4 (R4.1)
/i.MX6ULL MAIN/LCD/LCD_R4: CN5.38, RN7.3 (R3.1)
/i.MX6ULL MAIN/LCD/LCD_R5: CN5.39, RN7.2 (R2.1)
/i.MX6ULL MAIN/LCD/LCD_R6: CN5.40, RN7.1 (R1.1)
/i.MX6ULL MAIN/LCD/LCD_R7: CN5.41, RN8.4 (R4.1)
/i.MX6ULL MAIN/LCD/LCD_SCLK: CN5.16, RN1.1 (R1.1)
/i.MX6ULL MAIN/LCD/LCD_TOUCH_X1: CN5.6, R104.2
/i.MX6ULL MAIN/LCD/LCD_TOUCH_X2: CN5.8, R107.2
/i.MX6ULL MAIN/LCD/LCD_TOUCH_Y1: CN5.7, R105.2
/i.MX6ULL MAIN/LCD/LCD_TOUCH_Y2: CN5.9, R108.2
/i.MX6ULL MAIN/LCD/LCD_VCOM: CN5.56, CN5.57, R126.2
/i.MX6ULL MAIN/LCD/LCD_VDD: CN5.47, CN5.48, R119.2
/i.MX6ULL MAIN/LCD/VCOM_M: R127.2, RN1.5 (R4.2)
/i.MX6ULL MAIN/LCD/VSUP: C129.2, C131.1, C132.1, D16.3 (common), D18.1 (A), R113.1, U18.9 (SUP)
/i.MX6ULL MAIN/RAM DDR3/DRAM_DATA0: TP27.1, U7.T4 (DRAM_DATA00), U9.E3 (DQL0)
/i.MX6ULL MAIN/RAM DDR3/DRAM_DATA1: U7.U6 (DRAM_DATA01), U9.F7 (DQL1)
/i.MX6ULL MAIN/RAM DDR3/DRAM_DATA2: U7.T6 (DRAM_DATA02), U9.F2 (DQL2)
/i.MX6ULL MAIN/RAM DDR3/DRAM_DATA3: U7.U7 (DRAM_DATA03), U9.F8 (DQL3)
/i.MX6ULL MAIN/RAM DDR3/DRAM_DATA4: U7.U8 (DRAM_DATA04), U9.H3 (DQL4)
/i.MX6ULL MAIN/RAM DDR3/DRAM_DATA5: U7.T8 (DRAM_DATA05), U9.H8 (DQL5)
/i.MX6ULL MAIN/RAM DDR3/DRAM_DATA6: U7.T5 (DRAM_DATA06), U9.G2 (DQL6)
/i.MX6ULL MAIN/RAM DDR3/DRAM_DATA7: U7.U4 (DRAM_DATA07), U9.H7 (DQL7)
/i.MX6ULL MAIN/RAM DDR3/DRAM_DATA8: U7.U2 (DRAM_DATA08), U9.D7 (DQU0)
/i.MX6ULL MAIN/RAM DDR3/DRAM_DATA9: U7.U3 (DRAM_DATA09), U9.C3 (DQU1)
/i.MX6ULL MAIN/RAM DDR3/DRAM_DATA10: U7.U5 (DRAM_DATA10), U9.C8 (DQU2)
/i.MX6ULL MAIN/RAM DDR3/DRAM_DATA11: U7.R4 (DRAM_DATA11), U9.C2 (DQU3)
/i.MX6ULL MAIN/RAM DDR3/DRAM_DATA12: U7.P5 (DRAM_DATA12), U9.A7 (DQU4)
/i.MX6ULL MAIN/RAM DDR3/DRAM_DATA13: U7.P3 (DRAM_DATA13), U9.A2 (DQU5)
/i.MX6ULL MAIN/RAM DDR3/DRAM_DATA14: U7.R2 (DRAM_DATA14), U9.B8 (DQU6)
/i.MX6ULL MAIN/RAM DDR3/DRAM_DATA15: U7.R1 (DRAM_DATA15), U9.A3 (DQU7)
/i.MX6ULL MAIN/RAM DDR3/DRAM_DML: U7.T7 (DRAM_DQM0), U9.E7 (DML)
/i.MX6ULL MAIN/RAM DDR3/DRAM_DMU: U7.T3 (DRAM_DQM1), U9.D3 (DMU)
/i.MX6ULL MAIN/RAM DDR3/DRAM_DQSL_N: U7.P7 (DRAM_SDQS0_N), U9.G3 (~DQSL)
/i.MX6ULL MAIN/RAM DDR3/DRAM_DQSL_P: U7.P6 (DRAM_SDQS0_P), U9.F3 (DQSL)
/i.MX6ULL MAIN/RAM DDR3/DRAM_DQSU_N: U7.T2 (DRAM_SDQS1_N), U9.B7 (~DQSU)
/i.MX6ULL MAIN/RAM DDR3/DRAM_DQSU_P: U7.T1 (DRAM_SDQS1_P), U9.C7 (DQSU)
/i.MX6ULL MAIN/RAM DDR3/~DRAM_RESET: R18.1, R43.1, U7.G4 (DRAM_RESET), U9.T2 (~RESET)
/i.MX6ULL MAIN/eMMC QSPI SD/eMMC_VDDI: C86.1, U10.C2 (VDDI)
DRAM_VREF: C54.1, C78.2, C79.1, R46.2, R47.1, TP25.1, U7.P4 (DRAM_VREF), U9.H1 (VREFDQ), U9.M8 (VREFCA)
GNDREF: C1.2, C2.2, C4.2, C5.2, C6.2, C7.2, C8.2, C9.2, C12.2, C13.2, C14.2, C15.2, C16.2, C18.2, C19.2, C20.2, C22.2, C23.2, C24.2, C25.2, C26.2, C27.2, C28.2, C29.2, C30.2, C31.2, C32.2, C33.2, C34.2, C35.2, C36.2, C37.2, C38.2, C39.2, C40.2, C41.2, C42.2, C43.2, C44.2, C45.2, C46.2, C50.2, C51.2, C52.2, C53.2, C54.2, C55.2, C56.2, C57.2, C58.2, C59.2, C60.2, C61.2, C62.2, C63.2, C64.2, C65.2, C66.2, C67.2, C68.2, C69.2, C70.2, C71.2, C72.2, C73.2, C74.2, C75.2, C76.2, C77.2, C79.2, C80.2, C81.2, C82.2, C83.2, C84.2, C85.2, C86.2, C87.2, C88.2, C89.2, C90.2, C91.2, C92.2, C93.2, C94.1, C95.1, C96.2, C97.1, C98.2, C99.1, C100.1, C101.1, C102.1, C103.1, C104.1, C105.2, C106.2, C107.2, C108.2, C109.1, C110.1, C111.1, C112.1, C113.1, C115.2, C116.2, C117.1, C118.2, C119.2, C120.2, C121.2, C122.2, C123.2, C124.2, C125.2, C126.2, C127.2, C128.1, C131.2, C132.2, C134.1, C135.1, C136.2, C137.1, C138.1, C139.2, C141.2, C142.1, C143.2, C144.2, C145.2, C146.2, C147.2, C148.2, C149.2, C150.2, C151.2, C152.2, C153.2, C154.2, C155.1, CN1.2 (S), CN2.2 (S), CN5.3, CN5.4, CN5.5, CN5.10, CN5.58, CN5.59, CN5.60, CN5.MP, CN6.1 (GND), CN6.12 (GND), CN6.SH (SHIELD), CN7.4, CN7.6, CN7.8, CN7.10, CN7.12, CN7.14, CN7.16, CN7.18, CN7.20, D1.1 (A1), D2.1 (A1), D3.1 (A1), D4.1 (A1), D5.1 (A1), D6.1 (A1), D7.2 (A2), D8.2 (A2), D9.2 (A2), D10.2 (A2), D11.1 (A1), D12.1 (A1), D13.1 (A1), D14.1 (A1), D17.2 (K), D19.1 (A1), D22.1 (A1), D23.1 (A1), D24.1 (K), H1.1, H2.1, H3.1, J1.6 (VSS), J1.10 (SH), J2.8 (GND), J2.15 (GND), J2.16 (GND), J3.0 (SHEELD), J3.4 (GND), J4.0 (SHEELD), J4.4 (GND), PB1.1, PB2.1, Q2.2 (E), Q3.2 (E), Q4.2 (E), Q5.2 (E), Q6.2 (E), R2.2, R6.2, R7.2, R8.2, R14.2, R16.2, R17.2, R18.2, R19.2, R20.2, R25.1, R27.1, R28.1, R29.2, R30.1, R31.1, R32.1, R33.1, R34.1, R35.1, R36.1, R37.1, R41.2, R42.2, R43.2, R44.2, R45.2, R47.2, R57.2, R58.2, R65.2, R69.2, R70.2, R71.2, R75.2, R76.2, R77.2, R80.2, R81.2, R82.2, R83.2, R85.2, R86.1, R89.1, R90.1, R91.1, R94.1, R97.1, R98.2, R102.2, R109.1, R115.2, R121.1, R129.1, R130.1, R157.2, R158.2, R159.2, R160.2, R161.2, R162.2, R163.2, R164.2, R165.2, R166.2, R167.2, R168.2, R169.2, R170.2, R171.2, R172.2, R173.2, R174.2, R175.2, R176.2, R177.2, R178.2, R179.2, R180.2, R189.2, R190.2, R201.2, R202.2, R212.2, TP15.1, TP19.1, TP24.1, TP29.1, TP30.1, TP31.1, TP35.1, U1.2 (GND), U2.2 (GND), U3.2 (GND), U4.2 (GND), U5.2 (GND), U6.2 (GND), U7.A1 (VSS), U7.A17 (VSS), U7.C3 (VSS), U7.C7 (VSS), U7.C11 (VSS), U7.C15 (VSS), U7.E8 (VSS), U7.E11 (VSS), U7.F6 (VSS), U7.F7 (VSS), U7.F8 (VSS), U7.F9 (VSS), U7.F10 (VSS), U7.F11 (VSS), U7.F12 (VSS), U7.G3 (VSS), U7.G5 (VSS), U7.G7 (VSS), U7.G12 (VSS), U7.G15 (VSS), U7.H7 (VSS), U7.H12 (VSS), U7.J5 (VSS), U7.J7 (VSS), U7.J12 (VSS), U7.K7 (VSS), U7.K12 (VSS), U7.L3 (VSS), U7.L7 (VSS), U7.L12 (VSS), U7.M7 (VSS), U7.M8 (VSS), U7.M9 (VSS), U7.M10 (VSS), U7.M11 (VSS), U7.M12 (NGND_KEL0), U7.N3 (VSS), U7.N5 (VSS), U7.R3 (VSS), U7.R5 (VSS), U7.R7 (VSS), U7.R11 (VSS), U7.R16 (VSS), U7.R17 (VSS), U7.T14 (VSS), U7.U1 (VSS), U7.U14 (VSS), U7.U17 (VSS), U8.1 (GND), U9.A9 (VSS), U9.B1 (VSSQ), U9.B3 (VSS), U9.B9 (VSSQ), U9.D1 (VSSQ), U9.D8 (VSSQ), U9.E1 (VSS), U9.E2 (VSSQ), U9.E8 (VSSQ), U9.F9 (VSSQ), U9.G1 (VSSQ), U9.G8 (VSS), U9.G9 (VSSQ), U9.J2 (VSS), U9.J8 (VSS), U9.M1 (VSS), U9.M9 (VSS), U9.P1 (VSS), U9.P9 (VSS), U9.T1 (VSS), U9.T9 (VSS), U10.A6 (VSS), U10.C4 (VSSQ), U10.E7 (VSS), U10.G5 (VSS), U10.H10 (VSS), U10.J5 (VSS), U10.K8 (VSS), U10.N2 (VSSQ), U10.N5 (VSSQ), U10.P4 (VSSQ), U10.P6 (VSSQ), U11.4 (VSS), U12.17 (GND), U13.2 (GND), U14.2 (GND), U15.1 (GND), U15.33 (GND), U16.5 (DGND), U16.9 (CPGND), U16.14 (HPOUTFB), U16.17 (LINEOUTFB), U16.22 (AGND), U16.33 (GND_EP), U17.2 (GND), U18.7 (PGND), U18.8 (PGND), U18.19 (GND), U18.25 (EP), U19.2 (V-), U20.2 (GND), U21.3 (GND), U21.13 (GND), U21.21 (GND), U22.8 (GND), Y1.2, Y1.4
LCD_AVDD: C142.2, R117.1, R122.2, U18.10 (VCOM), U19.5 (V+)
LCD_VGH: C143.1, R123.1, U18.15 (VGH)
LCD_VGL: C128.2, D17.1 (A), R114.1, R120.1
unnamed: C65.1, R39.1, R40.1, Y1.1
unnamed: C104.2, R87.1
unnamed: C110.2, R88.1
unnamed: C112.2, R95.1
unnamed: C117.2, R96.1
unnamed: C123.1, R106.2
unnamed: C124.1, R111.2
unnamed: CN5.45, CN5.46, R117.2
unnamed: CN5.50, CN5.51, R120.2
unnamed: CN5.53, R123.2
unnamed: CN6.4 (CC1), R190.1
unnamed: CN6.10 (CC2), R189.1
unnamed: D1.2 (A2), FB4.2, J3.1 (VBUS)
unnamed: D4.2 (A2), FB5.2, J4.1 (VBUS)
unnamed: CN1.8 (T), D7.1 (A1), R86.2, R87.2, U16.13 (HPOUTL)
unnamed: CN1.6 (S), D8.1 (A1), R88.2, R89.2, U16.15 (HPOUTR)
unnamed: CN2.8 (T), D9.1 (A1), R94.2, R95.2, U16.16 (LINEOUTL)
unnamed: CN2.6 (S), D10.1 (A1), R96.2, R97.2, U16.18 (LINEOUTR)
unnamed: D15.1 (A), L4.2, R106.1
unnamed: C120.1, C121.1, D15.3 (common), Q1.2 (S), R102.1, R103.1
unnamed: D16.1 (A), L4.1, L4.4, R111.1, U18.5 (SW), U18.6 (SW)
unnamed: C130.1, D17.3 (common)
unnamed: C139.1, D18.2 (K), R118.1, U18.16 (CPI)
unnamed: C133.2, D18.3 (common)
unnamed: D20.2 (A), R187.1
unnamed: D21.2 (A), R188.1
unnamed: D24.2 (A), R191.2
unnamed: D25.2 (A), R192.2
unnamed: D25.1 (K), Q3.3 (C)
unnamed: D26.2 (A), R193.2
unnamed: D26.1 (K), Q4.3 (C)
unnamed: D27.2 (A), R194.2
unnamed: D27.1 (K), Q5.3 (C)
unnamed: D28.2 (A), R195.2
unnamed: D28.1 (K), Q6.3 (C)
unnamed: D30.2 (A), R203.2
unnamed: D30.1 (K), U22.15 (QA)
unnamed: D31.2 (A), R204.2
unnamed: D31.1 (K), U22.1 (QB)
unnamed: D32.2 (A), R205.2
unnamed: D32.1 (K), U22.2 (QC)
unnamed: D33.2 (A), R206.2
unnamed: D33.1 (K), U22.3 (QD)
unnamed: D34.2 (A), R207.2
unnamed: D34.1 (K), U22.4 (QE)
unnamed: D35.2 (A), R208.2
unnamed: D35.1 (K), U22.5 (QF)
unnamed: D36.2 (A), R209.2
unnamed: D36.1 (K), U22.6 (QG)
unnamed: D37.2 (A), R210.2
unnamed: D37.1 (K), U22.7 (QH)
unnamed: J1.2 (CD/DAT3), U12.15 (CH2)
unnamed: J1.5 (CLK), U12.13 (CH4)
unnamed: J1.3 (CMD), U12.14 (CH3)
unnamed: J1.7 (DAT0), U12.12 (CH5)
unnamed: J1.8 (DAT1), U12.11 (CH6)
unnamed: J1.1 (DAT2), U12.16 (CH1)
unnamed: C87.1, C88.1, FB3.2, J1.4 (VDD)
unnamed: J1.9 (~CD), U12.9 (CH8)
unnamed: J2.10 (GK), R63.2
unnamed: C99.2, J2.5 (RC)
unnamed: J2.3 (RD+), U15.5 (RXP)
unnamed: J2.6 (RD-), U15.4 (RXM)
unnamed: C100.2, J2.4 (TC)
unnamed: J2.1 (TD+), U15.7 (TXP)
unnamed: J2.2 (TD-), U15.6 (TXM)
unnamed: J2.11 (YK), R64.2
unnamed: Q1.3 (D), R99.1, R100.1, R101.1
unnamed: Q1.1 (G), R103.2, R109.2, R110.2
unnamed: Q2.1 (B), R112.2
unnamed: Q2.3 (C), R110.1
unnamed: Q3.1 (B), R197.1
unnamed: Q4.1 (B), R198.1
unnamed: Q5.1 (B), R199.1
unnamed: Q6.1 (B), R200.1
unnamed: R13.2, R14.1
unnamed: R126.1, R128.2, U19.4
unnamed: R151.2, SW1.8
unnamed: R152.2, SW1.7
unnamed: R153.2, SW1.6
unnamed: R154.2, SW1.5
unnamed: R155.2, SW2.8
unnamed: R156.2, SW2.7
unnamed: C3.1, R1.1, R2.1, U1.4 (ADJ)
unnamed: C13.1, R10.2, U2.4 (EN)
unnamed: R7.1, U2.3 (SET)
unnamed: C5.1, C6.1, C14.1, C18.1, R3.1, R9.1, R11.1, TP2.1, U2.1 (VOUT), U3.3 (VIN), U5.3 (VIN), U6.3 (VIN)
unnamed: C12.1, R9.2, U3.5 (EN)
unnamed: C10.1, R5.1, R8.1, U3.1 (FB)
unnamed: L1.1, U3.4 (LX)
unnamed: C22.1, R3.2, U3.6 (PG), U4.3 (EN), U5.5 (EN), U6.5 (EN)
unnamed: C11.1, R4.1, R6.1, U4.4 (ADJ)
unnamed: C17.1, R12.1, R13.1, U5.1 (FB)
unnamed: L2.1, U5.4 (LX)
unnamed: C21.1, R15.1, R16.1, U6.1 (FB)
unnamed: L3.1, U6.4 (LX)
unnamed: C51.1, C52.1, FB2.2, U7.L13 (VDDA_ADC_3P3), U7.M13 (ADC_VREFH)
unnamed: C37.1, C38.1, FB1.2, U7.N13 (VDD_HIGH_IN)
unnamed: R17.1, U7.N4 (DRAM_ZQPAD)
unnamed: TP20.1, U7.M17 (GPIO1_IO05)
unnamed: TP21.1, U7.K17 (GPIO1_IO06)
unnamed: TP22.1, U7.N17 (GPIO1_IO08)
unnamed: TP23.1, U7.M15 (GPIO1_IO09)
unnamed: R38.1, U7.F14 (ENET1_TX_CLK)
unnamed: C60.1, C61.1, U7.R12 (VDD_USB_CAP)
unnamed: TP14.1, U7.P16 (CCM_CLK1_N)
unnamed: TP13.1, U7.P17 (CCM_CLK1_P)
unnamed: TP16.1, U7.U9 (CCM_PMIC_STBY_REQ)
unnamed: R29.1, U7.P15 (JTAG_MOD)
unnamed: C68.1, U7.T11 (RTC_XTAL_I), Y2.2
unnamed: C67.1, U7.U11 (RTC_XTAL_O), Y2.1
unnamed: R27.2, U7.R10 (SNVS_TAMPER0)
unnamed: R28.2, U7.R9 (SNVS_TAMPER1)
unnamed: R30.2, U7.P11 (SNVS_TAMPER2)
unnamed: R31.2, U7.P10 (SNVS_TAMPER3)
unnamed: R32.2, U7.P9 (SNVS_TAMPER4)
unnamed: R26.2, R33.2, U7.N8 (SNVS_TAMPER5)
unnamed: R34.2, U7.N11 (SNVS_TAMPER6)
unnamed: R35.2, U7.N10 (SNVS_TAMPER7)
unnamed: R36.2, U7.N9 (SNVS_TAMPER8)
unnamed: R37.2, U7.R6 (SNVS_TAMPER9)
unnamed: R25.2, U7.N7 (TEST_MODE)
unnamed: TP18.1, U7.J16 (UART2_RX_DATA)
unnamed: TP17.1, U7.J17 (UART2_TX_DATA)
unnamed: C66.1, R40.2, U7.T16 (XTAL_I), Y1.3
unnamed: R39.2, U7.T17 (XTAL_O)
unnamed: R22.1, U8.2 (~RESET)
unnamed: R41.1, U9.L9 (NC_(ZQ1))
unnamed: R42.1, U9.L8 (ZQ0)
unnamed: R57.1, U13.3 (SET)
unnamed: R58.1, U14.3 (SET)
unnamed: R65.1, U15.10 (REXT)
unnamed: C95.2, C96.1, FB6.1, U15.3 (VDDA_3.3)
unnamed: C105.1, C106.1, FB7.2, U16.23 (AVDD)
unnamed: C114.2, U16.8 (CPCA)
unnamed: C114.1, U16.10 (CPCB)
unnamed: C116.1, U16.12 (CPVOUTN)
unnamed: C115.1, U16.11 (CPVOUTP)
unnamed: TP36.1, U16.1 (GPIO1_/_IRQ)
unnamed: R90.2, U16.27 (IN1L_/_DMICDAT1)
unnamed: R91.2, U16.25 (IN1R_/_DMICDAT2)
unnamed: C111.2, U16.20 (MICBIAS)
unnamed: C113.2, U16.21 (VMIDC)
unnamed: R98.1, U17.3 (SET)
unnamed: C136.1, U18.14 (ADJ)
unnamed: C134.2, U18.22 (COMP)
unnamed: R124.1, U18.13 (CTRL)
unnamed: C137.2, U18.2 (DLY1)
unnamed: C138.2, U18.3 (DLY2)
unnamed: C130.2, U18.18 (DRVN)
unnamed: C133.1, U18.17 (DRVP)
unnamed: C129.1, R113.2, R115.1, U18.1 (FB)
unnamed: R114.2, R116.1, U18.21 (FBN)
unnamed: R118.2, R121.2, U18.12 (FBP)
unnamed: C140.2, U18.24 (FDLY)
unnamed: C141.1, R125.1, U18.11 (IN)
unnamed: C135.2, R116.2, U18.20 (REF)
unnamed: C125.1, C126.1, C127.1, FB8.2, L4.3, U18.4 (VIN)
unnamed: R122.1, R129.2, R130.2, U19.1 (+)
unnamed: R127.1, R128.1, U19.3 (-)
unnamed: R182.1, U20.5 (A1)
unnamed: R184.1, U20.4 (A2)
unnamed: R181.2, U20.8 (B1)
unnamed: R183.2, U20.1 (B2)
unnamed: R186.2, U21.9 (USBDM)
unnamed: R185.2, U21.8 (USBDP)
unnamed: C153.1, C154.1, FB9.2, U21.12 (VCC)
unnamed: R211.2, R212.1, U22.13 (~OE)

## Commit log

2024-06-02 Add PCB Rev 00
2024-11-27 Change schematic and PCB
    changed component U11 from 8MBit to 32 MBit
    added qr-code on bottom overlay
2024-12-30 Add u-boot submodule
2024-12-30 Add U-Boot compilation instructions
2025-01-29 Add hardware issues in README.md
    Add section with issues found during hardware debug.
2026-02-16 Fix hardware bugs - Fix part number in bom for resistors R103, R113, R114, R118 -> 680K - Fix part number in BOM for resistors R13, R16 -> 68K - Fix part number in BOM for resistor R14 -> 4.7K - Fix 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
2026-02-16 Fix interactive BOM link
